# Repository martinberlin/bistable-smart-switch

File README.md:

**IMPORTANT:** This repository contains components added as github submodules. Please clone it using

    git clone --recurse-submodules https://github.com/martinberlin/bistable-smart-switch.git
        or if you already cloned it without them just run additionally:
    git submodule update --init --recursive

# Bistable-smart-switch

This is a project that started with the idea to use small, and inexpensive, SPI epapers with touch. The ones that I've found available and met that criteria are produced by Good-Display in Dalian.
The idea is very simple: 

> Use this bistable displays, or any others with very low consumption, to design a Switch that can replace a standard European one.

I know is a lot of technology to turn on the light and at some point I though that no-one will buy a digital switch for a spaceship.

**But it turns out that it got some attention since there are some interesting points that drive this:**

- **ESP32-C3** is also an unexpensive, single Core, RISC-V Espressif MCU with 4 MB flash and the usual BLE/ WiFi combination
- **Having touch and UX with a bistable display**, using our own component CalEPD and our own touch fork, gives us the freedom to be Code-light and make versatile examples that everyone can extend and collaborate
- **ESP-Rainmaker** is a possibility that we already tested, so you can also turn ON/OFF the light with their application
- **There are no similar smart switches** that come with full schematics, PCB's and example Firmware. If there are please tell us where since I'm interested to see what others are doing (We know already jung.de the zamel.com polish brand and more) But none of them offers a hackeable switch.

All that we have already but it was around different repositories, where you had to configure CMakeFiles to point it to the right example and more...
The goal of this repo is to put all this Switch ideas and code demos in a single place, make a WiKi with configuration tutorials and documentation. Just make it easy for the user to get started and build his first working Firmware in 10 minutes.

With the current hardware and demo examples what you can do is straight-forward. You can design a switch, since we provide a very basic example, and detect touch X & Y events. Based on that you can send signals to the Latch relay PCB and move the switch to the ON or OFF position.
But is your switch. You could draw something using GFX over. Soon we will add examples to load images from WiFi and other cool things. And Latch relay is low consumption, you just move it with a 50 ms signal, then it stays in that position.
It has no way to tell in what position is from outside but we know it since by default the ESP32 C3 moves it to OFF as the Firmware starts.

## The hardware

It consists in two PCBs and the display using C3 as Microcontroller:

1. **ESP32-C3 controller with touch**
2. **220AC to 3.3DC adapter with a Latch relay switch**. 54x54 mm so it fits in the small black box inside the wall Can be also a solid-state relay or you can design your own
3. **The 2.7" display** with touch [GDEY027T91-T](https://github.com/martinberlin/cale-idf/wiki/Good-Display-gdey027T91)

This is the touch panel that comes already on top of the display. Check the [GOODISPLAY product page](https://www.good-display.com/product/2.7-inch-touch-screen,-for-2.7-inch-e-paper-display-259.html) for specifications and datasheet.

More pictures and documentation will be added in the WiKi section, that is better to keep things organized and inter-linked than a single readme page.

## IO configuration

We will keep mostly the same "proven to work" IOs along the PCB versions but it might be that routing is simpler using different pins for SPI. To keep it organized the default sdkconfig will point to PCB latest release (In this case 1.1) and we will keep track of the right IO config for different versions in the [sdk-config-board](sdk-config-board) directory.

As an example if you have a 1.0 PCB, you can simply cp that sdkconfig to your project one doing this from the project root folder:

    $ cp sdk-config-board/1.0/sdkconfig .

Alternatively you can configure this the usual way with ESP-IDF using menuconfig:

    idf.py menuconfig

    SPI configuration is located in: **Component config → SPI epaper configuration**

    I2C and RTC configuration: **Root → RTC & I2C Configuration**

    WiFi connection for RTC sync: **Root → Example Connection Configuration**

## The code examples

1. [Getting started](main/switch/getting-started) a simple ON-OFF basic switch. No configuration required.

More will soon land here. For the moment they are in mother repository cale-idf that is an incredible mess where I develop the components and is full of examples, that I promised myself to reorganize, and I will probably never do.
Just be patient, life takes it's times, just like the hardware design part and examples.

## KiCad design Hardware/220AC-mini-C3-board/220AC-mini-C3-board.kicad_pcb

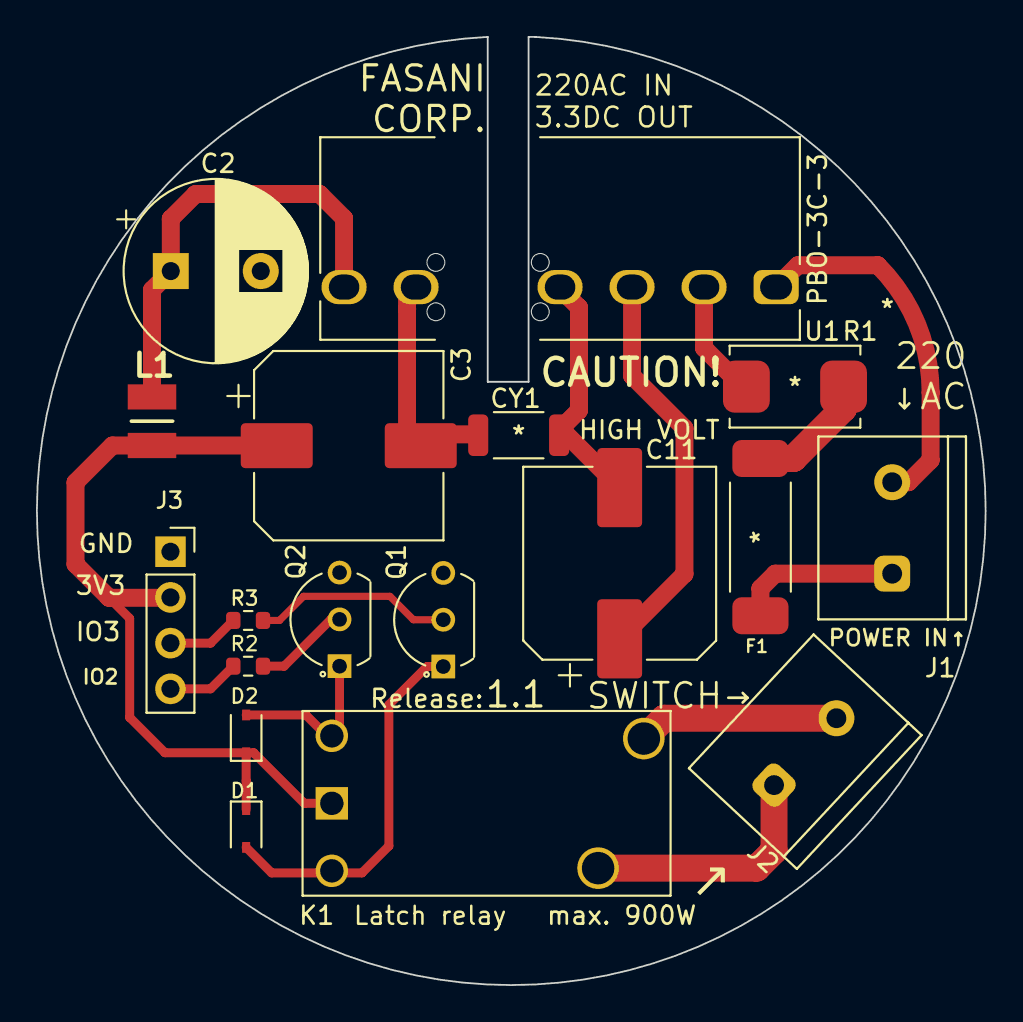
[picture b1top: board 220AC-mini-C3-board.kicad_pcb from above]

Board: 2 copper layers, 52.7 x 52.7 mm, 18 parts (0 on the bottom side), 17 nets.

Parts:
C2: 470uF; CP_Radial_D10.0mm_P5.00mm
C3: C 150uF; CP_Elec_10x10
C11: 12uF; CP_Elec_10x14.3
CY1: 1nF; CC1808KKX7RCBB102
D1, D2: 1N4148; D_SOD-323
F1: Fuse; 0443001.DR
J1: AC MAINS POWER; Conn_C8269
J2: ON/OFF switch; Conn_C8269
J3: Conn_01x04; PinSocket_1x04_P2.54mm_Vertical
K1: HF163-F; FH44L-1AT-L2-DC3V
L1: L; IND_BRL3225T4R7M
Q1, Q2: Q_NPN_CBE; BC547B
R1: R; SMW212RJT
R2, R3: 430Ω; R_0603_1608Metric
U1: PBO-3C-3

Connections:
+3V3: C3.1, D1.1 (K), D2.1 (K), J3.2, K1.2, L1.2
/AC (N): J1.2, U1.1 (ACL)
/IO_2: J3.4, R2.2
/IO_3: J3.3, R3.2
AC: F1.1, J1.1
GND: C2.2, C3.2, CY1.1, J3.1, Q1.3 (E), Q2.3 (E), U1.5 (-VO)
unnamed: C11.1, U1.3 (+VCAP)
unnamed: C11.2, CY1.2, U1.4 (-VCAP)
unnamed: C2.1, L1.1, U1.6 (+VO)
unnamed: D1.2 (A), K1.1, Q1.1 (C)
unnamed: D2.2 (A), K1.3, Q2.1 (C)
unnamed: F1.2, R1.1
unnamed: J2.1, K1.5
unnamed: J2.2, K1.4
unnamed: Q1.2 (B), R3.1
unnamed: Q2.2 (B), R2.1
unnamed: R1.2, U1.2 (ACN)

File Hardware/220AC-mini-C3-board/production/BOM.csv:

"Id";"Designator";"Package";"Quantity";"Designation";"Supplier and ref";
1;"J1";"1729128-screw-terminal";1;"AC MAINS POWER";;;
2;"R1";"SMW212RJT";1;"R";;;
3;"C1,C11";"CP_Elec_10x14.3";2;"12uF";;;
4;"K1";"HF163FL24HL2T";1;"HF163-F";;;
5;"D2,D1";"D_SOD-323";2;"1N4148";;;
6;"CY1";"CC1808KKX7RCBB102";1;"1nF";;;
7;"U1";"PBO-3C-3";1;"PBO-3C-3";;;
8;"Q1,Q2";"BC547B";2;"Q_NPN_CBE";;;
9;"C2";"CP_Radial_D10.0mm_P5.00mm";1;"470uF";;;
10;"F1";"0443001.DR";1;"Fuse";;;
11;"J2";"1729128-screw-terminal";1;"ON/OFF switch";;;
12;"C3";"CP_Elec_10x10";1;"C 150uF";;;
13;"L1";"SMDRI127-470MT";1;"L";;;
14;"J3";"PinSocket_1x04_P2.54mm_Vertical";1;"Conn_01x04";;;

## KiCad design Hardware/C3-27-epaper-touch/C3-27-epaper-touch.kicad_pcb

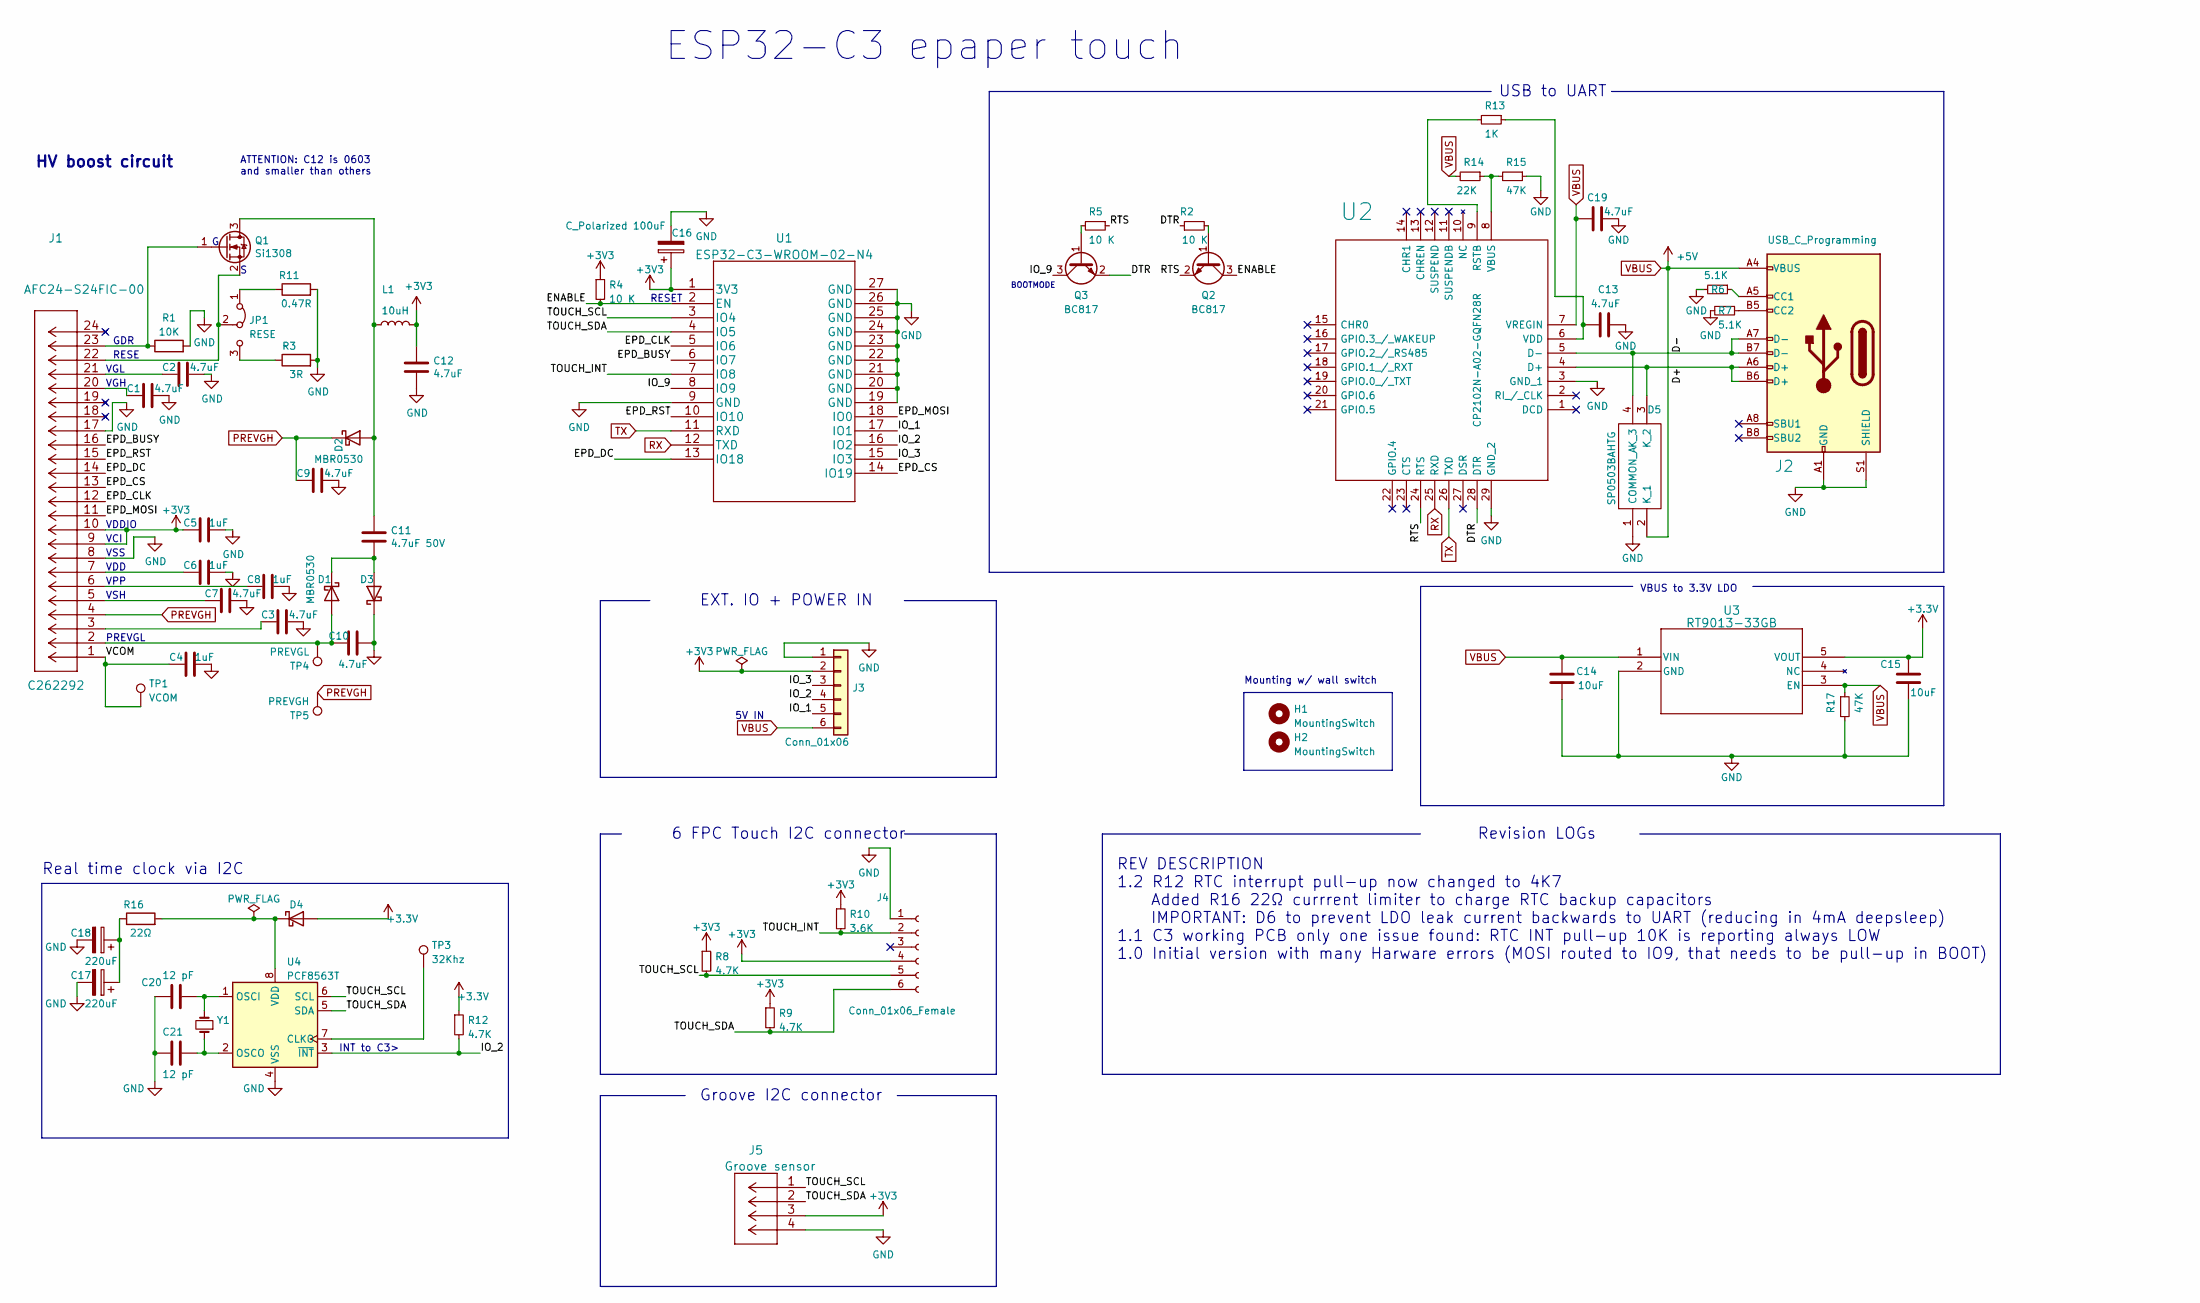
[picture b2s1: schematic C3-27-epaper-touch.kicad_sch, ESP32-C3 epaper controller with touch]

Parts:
C1, C2, C3, C7, C9, C10, C19: 4.7uF; C_0805_2012Metric_Pad1.18x1.45mm_HandSolder; LCSC C1779
C4, C5, C6, C8: 1uF; C_0805_2012Metric_Pad1.18x1.45mm_HandSolder; LCSC C28323
C11: 4.7uF 50V; C_0805_2012Metric_Pad1.18x1.45mm_HandSolder; LCSC C1779
C12: 4.7uF; C_0603_1608Metric; LCSC C19666
C13: 4.7uF; C_0805_2012Metric; LCSC C1779
C14, C15: 10uF; C_0805_2012Metric; LCSC C15850
C16: C_Polarized 100uF; CP_EIA-3528-21_Kemet-B; LCSC C129289
C17, C18: 220uF; CP_EIA-3528-21_Kemet-B; LCSC C122252
C20, C21: 12 pF; C_0603_1608Metric; LCSC C38523
D1, D2, D3: MBR0530; D_SOD-123; LCSC C77336
D4: 1N5819WS; D_SOD-323; LCSC C191023
D5: SP0503BAHTG; Manufacturer_Part_Number SP0503BAHTG; LCSC C3040626
H1, H2: MountingSwitch; MountingHole_3.2mm_M3
J1: AFC24-S24FIC-00
J2: USB_C_Programming; USB_C_Receptacle_HRO_TYPE-C-31-M-12; LCSC C165948
J3: Conn_01x06; PinSocket_1x06_P2.54mm_Vertical
J4: Conn_01x06_Female; FH34SRJ-6S-0.5SH50-Hirose; LCSC C224194
J5: Groove sensor; MOLEX-I2C-Groove
JP1: RESE; switch-MK-12C02-G020; LCSC C2911519
L1: 10uH; SWPA4030S1R0NT; LCSC C38117
Q1: Si1308; SOT-323_SC-70; LCSC C469327
Q2, Q3: BC817; SOT-23; LCSC C146798
R1: 10K; R_0603_1608Metric; LCSC C25804
R2, R4, R5: 10 K; R_0603_1608Metric; LCSC C25804
R3: 3R; R_0603_1608Metric; LCSC C25237
R6, R7: 5.1K; R_0603_1608Metric; LCSC C23186
R8, R9, R12: 4.7K; R_0603_1608Metric; LCSC C23162
R10: 3.6K; R_0603_1608Metric; LCSC C22980
R11: 0.47R; R_0603_1608Metric; LCSC C103895
R13: 1K; R_0603_1608Metric; LCSC C21190
R14: 22K; R_0603_1608Metric; LCSC C31850
R15, R17: 47K; R_0603_1608Metric; LCSC C137715
R16: 22Ω; R_0603_1608Metric; LCSC C177566
TP1: VCOM; TestPoint_Pad_D1.5mm
TP3: 32Khz; TestPoint_Pad_D1.5mm
TP4: PREVGL; TestPoint_Pad_D1.5mm
TP5: PREVGH; TestPoint_Pad_D1.5mm
U1: ESP32-C3-WROOM-02-N4; LCSC C2934560
U2: CP2102N-A02-GQFN28R; CP2102-QFN50P500X500X80-29N-D; Manufacturer_Part_Number CP2102N-A02-GQFN28R; Mouser Part Number 634-CP2102NA02QFN28R
U3: RT9013-33GB
U4: PCF8563T; SOIC-8_3.9x4.9mm_P1.27mm; LCSC C7440
Y1: Crystal_Small; Q13FC1350000400-Crystal; LCSC C32346

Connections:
/D+: D5.3 (K_2), J2.A6 (D+), J2.B6 (D+), U2.4 (D+)
/D-: D5.4 (K_3), J2.A7 (D-), J2.B7 (D-), U2.5 (D-)
/DTR: Q3.2 (E), R2.1, U2.28 (DTR)
/ENABLE: Q2.3 (C), R4.2, U1.2 (EN)
/EPD_BUSY: J1.16, U1.6 (IO7)
/EPD_CLK: J1.12, U1.5 (IO6)
/EPD_CS: J1.13, U1.14 (IO19)
/EPD_DC: J1.14, U1.13 (IO18)
/EPD_MOSI: J1.11, U1.18 (IO0)
/EPD_RST: J1.15, U1.10 (IO10)
/IO_1: J3.5, U1.17 (IO1)
/IO_2: J3.4, R12.2, U1.16 (IO2), U4.3 (~INT)
/IO_3: J3.3, U1.15 (IO3)
/IO_9: Q3.3 (C), U1.8 (IO9)
/RTS: Q2.2 (E), R5.1, U2.24 (RTS)
/TOUCH_INT: J4.2, R10.2, U1.7 (IO8)
/TOUCH_SCL: J4.5, J5.1, R8.2, U1.3 (IO4), U4.6 (SCL)
/TOUCH_SDA: J4.6, J5.2, R9.2, U1.4 (IO5), U4.5 (SDA)
/VCOM: C4.2, J1.1, TP1.1
GND: C1.1, C2.1, C3.1, C4.1, C5.1, C6.1, C7.1, C8.1, C9.1, C10.1, C12.1, C13.2, C14.2, C15.2, C16.2, C17.2, C18.2, C19.1, C20.1, C21.1, D3.1 (K), D5.1 (COMMON_A), J1.8, J1.17, J2.A1 (GND), J2.A12 (GND), J2.B1 (GND), J2.B12 (GND), J2.S1 (SHIELD), J3.1, J4.1, J5.4, R1.2, R3.2, R6.2, R7.2, R11.2, R15.1, R17.2, U1.9 (GND), U1.19 (GND), U1.20 (GND), U1.21 (GND), U1.22 (GND), U1.23 (GND), U1.24 (GND), U1.25 (GND), U1.26 (GND), U1.27 (GND), U2.3 (GND_1), U2.29 (GND_2), U3.2 (GND), U4.4 (VSS)
unnamed: C1.2, J1.20
unnamed: C2.2, J1.21
unnamed: C3.2, J1.3
unnamed: C6.2, J1.7
unnamed: C7.2, J1.5
unnamed: C8.2, J1.6
unnamed: C17.1, C18.1, R16.1
unnamed: C10.2, D1.2 (A), J1.2, TP4.1
unnamed: C11.1, D1.1 (K), D3.2 (A)
unnamed: C11.2, D2.2 (A), L1.1, Q1.3 (D)
unnamed: D4.1 (K), R16.2, U4.8 (VDD)
unnamed: J2.A5 (CC1), R6.1
unnamed: J2.B5 (CC2), R7.1
unnamed: JP1.1 (A), R11.1
unnamed: JP1.3 (B), R3.1
unnamed: J1.22, JP1.2 (C), Q1.2 (S)
unnamed: J1.23, Q1.1 (G), R1.1
unnamed: Q2.1 (B), R2.2
unnamed: Q3.1 (B), R5.2
unnamed: R13.2, U2.9 (RSTB)
unnamed: R14.1, R15.2, U2.8 (VBUS)
unnamed: C13.1, R13.1, U2.6 (VDD)
unnamed: TP3.1, U4.7 (CLKO)
unnamed: C20.2, U4.1 (OSCI), Y1.2
unnamed: C21.2, U4.2 (OSCO), Y1.1
PREVGH: C9.2, D2.1 (K), J1.4, TP5.1
RX: U1.12 (TXD), U2.25 (RXD)
TX: U1.11 (RXD), U2.26 (TXD)
VBUS: C14.1, C19.2, D5.2 (K_1), J2.A4 (VBUS), J2.A9 (VBUS), J2.B4 (VBUS), J2.B9 (VBUS), J3.6, R14.2, R17.1, U2.7 (VREGIN), U3.1 (VIN), U3.3 (EN)

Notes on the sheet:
PREVGL
EXT. IO + POWER IN
RESE
VCI
VDDIO
REV DESCRIPTION 1.2 R12 RTC interrupt pull-up now changed to 4K7 Added R16 22Ω currrent limiter to charge RTC backup capacitors IMPORTANT: D6 to prevent LDO leak current backwards to UART (reducing in 4mA deepsleep) 1.1 C3 working PCB only one issue found: RTC INT pull-up 10K is reporting always LO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
Groove I2C connector
Revision LOGs
Real time clock via I2C
INT to C3>
BOOTMODE
5V IN
6 FPC Touch I2C connector
VDD
VSH
VSS
VPP
VGL
RESET
ATTENTION: C12 is 0603 and smaller than others
VGH
USB to UART
VBUS to 3.3V LDO
GDR
ESP32-C3 epaper touch
Mounting w/ wall switch
HV boost circuit

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
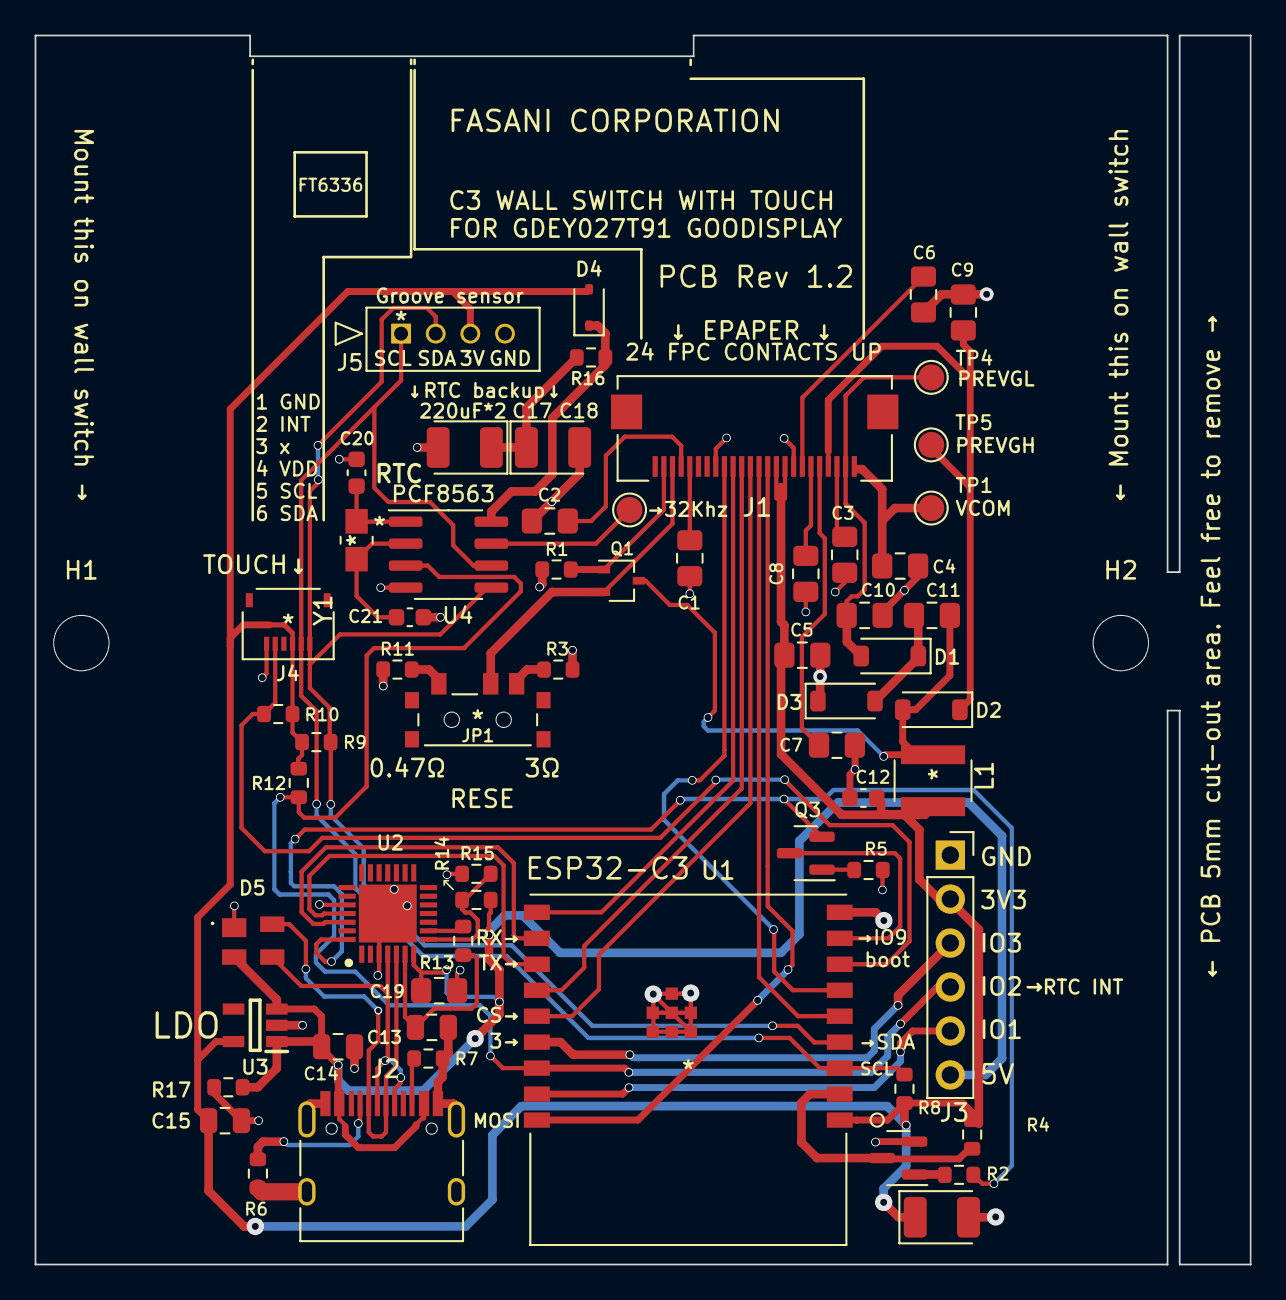
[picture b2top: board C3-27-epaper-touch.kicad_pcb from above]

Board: 4 copper layers, 70.2 x 71.0 mm, 64 parts (0 on the bottom side), 50 nets.

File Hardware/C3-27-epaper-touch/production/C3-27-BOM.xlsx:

Designator | Footprint | Comment | JLPCB Part#
D4 | D_SOD-323 | 1N5819WS | C191023
C2,C7,C9,C10,C19,C1,C3 | C_0805_2012Metric_Pad1.18x1.45mm_HandSolder | 4.7uF | C1779
Q2,Q3 | SOT-23 | BC817 | C146798
C8,C4,C6,C5 | C_0805_2012Metric_Pad1.18x1.45mm_HandSolder | 1uF | C28323
J2 | USB_C_Receptacle_HRO_TYPE-C-31-M-12 | USB_C_Programming | C165948
U3 | SOT-23 | MCP1700-3302E_SOT23 | C39051
R13 | R_0603_1608Metric | 1K | C21190
C11 | C_0805_2012Metric_Pad1.18x1.45mm_HandSolder | 4.7uF 50V | C1779
R11 | R_0603_1608Metric | 0.47R | C103895
C17,C18 | CP_EIA-3528-21_Kemet-B | 220uF | C122252
U4 | SOIC-8_3.9x4.9mm_P1.27mm | DS3231MZ | C107410
R3 | R_0603_1608Metric | 3R | C25237
R2,R5,R12,R4 | R_0603_1608Metric | 10 K | C25804
JP1 | switch-MK-12C02-G020 | RESE | C2911519
C14,C15 | C_0805_2012Metric | 10uF | C15850
J1 | AFC24-S24FIC-00 | AFC24-S24FIC-00 | C262292
R7,R6 | R_0603_1608Metric | 5.1K | C23186
D1,D3,D2 | D_SOD-123 | MBR0530 | C77336
C13 | C_0805_2012Metric | 100nF | C28233
R10 | R_0603_1608Metric | 3.6K | C22980
C16 | CP_EIA-3528-21_Kemet-B | C_Polarized 100uF | C129289
R1 | R_0603_1608Metric | 10K | C25804
J4 | FH34SRJ-6S-0.5SH50-Hirose | Conn_01x06_Female | C224194
R9,R8 | R_0603_1608Metric | 4.7K | C23162
U2 | CP2102-QFN50P500X500X80-29N-D | CP2102N-A02-GQFN28R | C964632
R15 | R_0402_1005Metric | 47K | C137974
Q1 | SOT-323_SC-70 | Si1308 | C469327
C12 | C_0603_1608Metric | 4.7uF | C19666
L1 | SWPA4030S1R0NT | 10uH | C38117
R14 | R_0201_0603Metric | 22K | C31850

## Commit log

2023-02-17 Start adding components
2023-02-18 Initial commit with basic example that builds
2023-02-18 Add Hardware section
2023-02-18 Update Hardware images
2023-02-18 Readme
2023-02-19 Add sdk-config-board example
2023-02-19 220AC 3.3DC adapter redesigned 1.1
2023-02-19 HW Add 3D models & update footprints
2023-02-19 Update kicad PCB
2023-02-19 Make revision folders also for production
2023-02-20 Hardware: S3 pro version idea
2023-02-20 S3 pro release 1.0
2023-02-20 Clear DRC errors
2023-02-20 S3: Do not use MOSI in JTAG data pins
2023-02-21 Add sdkconfig with S3 IOs
2023-02-21 Add also I2Cscanner example
2023-02-21 Add files via upload
    Changes
    R16 0R = IO46 Resistor for Compatibility to ESP32 WROOM
    R15 changed package to 0603(was 0402)
    Fixed Layout error at R15
    Rerouted RTS Line to enable 2 Layer Board
    Rerouted 3.3V next to J3
2023-02-22 Update R15 thx. @Uspizig
2023-02-22 #2 Add RTC get and set Clock examples
2023-02-22 Error detected by @ispizig. Thanks!
2023-02-23 #2 4 gray RTC idea
2023-02-23 #2 Implement easy minute counter
2023-02-23 #2 Tick every second like a clock
2023-02-23 #2 Store every minute passed in NVS. Restart from there in case of reset
2023-02-24 Move C3 version but w/PCF8563 RTC
2023-02-24 Update C3 schematic
2023-02-24 Update C15 put it closer to LDO
2023-02-25 C3 Rev 1.1 sent to fabrication
2023-02-25 C3 Rev 1.2 start: Simplify routing
2023-02-25 #2 Make RTC example better and auto-sync
2023-02-25 Mark properly D+ & D- lines
2023-02-25 #2 Add Rainmaker 1.0 version
2023-02-25 #2 Add WiFi clear credentials also in display
2023-02-26 Update 1.1 R14 & R15 VUSB sense CP2102
2023-02-26 C3 1.1 remove C13 does not seem to be necessary (near CP2102)
2023-02-26 Revert "C3 1.1 remove C13 does not seem to be necessary (near CP2102)"
    This reverts commit e9bbdf2bfd8dbd0aba68dd1d7c9680fb7645ba6f.
2023-02-26 C3 1.1 replace C13 to be 4.7uF
2023-02-26 C3 1.1 update Y1 crystal
2023-02-27 cambios CAF
2023-02-27 Make CAF refactoring pass schematics
2023-02-27 Update 3D and assign to latch relay
2023-02-27 Update silkscreen
2023-02-27 Update schematics
2023-02-27 C3 schematics keep up to date
2023-02-27 Remove innecesary GND since there is ground pane
2023-02-27 #7 Start adding Rainmaker UX
2023-02-28 #7 Further planning UX & params to be NVS stored
2023-02-28 #7 Thanks Piyush from Rainmaker team
2023-02-28 #7 Rainmaker UX ver 1.0 add EPD info
2023-02-28 #7 Reset counter should act also if switch is OFF
2023-03-01 #7 Reset counters differently DAY 1 00:00 Hrs
2023-03-01 #7 Nesting of IFs solved for secs counter
2023-03-01 H 220AC adapter silk
2023-03-01 #8 Add basic calculation to rtc/ds3231-switch.cpp
2023-03-02 draw_centered_text made better. Portrait mode added
2023-03-02 Exclude temperature (is not precise)
2023-03-04 S3 update to review: No more C 220uF RTC backup use CR1220
2023-03-07 Update S3 heading to 1.1 release
2023-03-07 #8 start adding PCF8563 RTC suport
2023-03-08 #8 PCF switch C3 version. Pending issues
2023-03-09 #8 PCF8563 switch is working and counting consumption by minute
2023-03-09 #8 1st version PCF8563 ready to be tested
2023-03-12 #8 Count also per seconds w/ PCF8563 RTC @goran-mahovlic
2023-03-15 C3 Rev 1.1 tests
2023-03-15 1.2 is ready, this time MCU can be soldered already
2023-03-17 C3 PCB add R16 current limiting for RTC backup CAPs
2023-03-18 Update schematics. Introduce Rev log
2023-03-18 Switch to updated PCF8563 component
2023-03-19 Implement dark mode
2023-03-19 Preprare grounds for new LDO in S3 version
2023-03-19 Start with buttons sample
2023-03-20 Correct edge-cuts for right FPC bending
2023-03-20 6 button demo
2023-03-22 Add 3D case file (Wall switch: 60 mm separated 3mm hole)
2023-03-22 Add 3D full sources including blend (er) file
2023-04-16 C3 PCB update RES label
2023-04-17 Optimize deepsleep for C3 version
2023-04-17 Switch LDO to RT9013-33GB Ref https://github.com/martinberlin/H-spi-adapters/issues/9
2023-04-17 Update C3 schematics with new LDO
2023-05-06 Do SET_CLOCK properly
2023-05-12 Update pcf8563 switch
2023-05-12 Update NTP config
2023-05-12 Update RTC_INT initial alert status

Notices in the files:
parts and their libraries:
Copyright 2021 Accelerated Designs. All rights reserved.
